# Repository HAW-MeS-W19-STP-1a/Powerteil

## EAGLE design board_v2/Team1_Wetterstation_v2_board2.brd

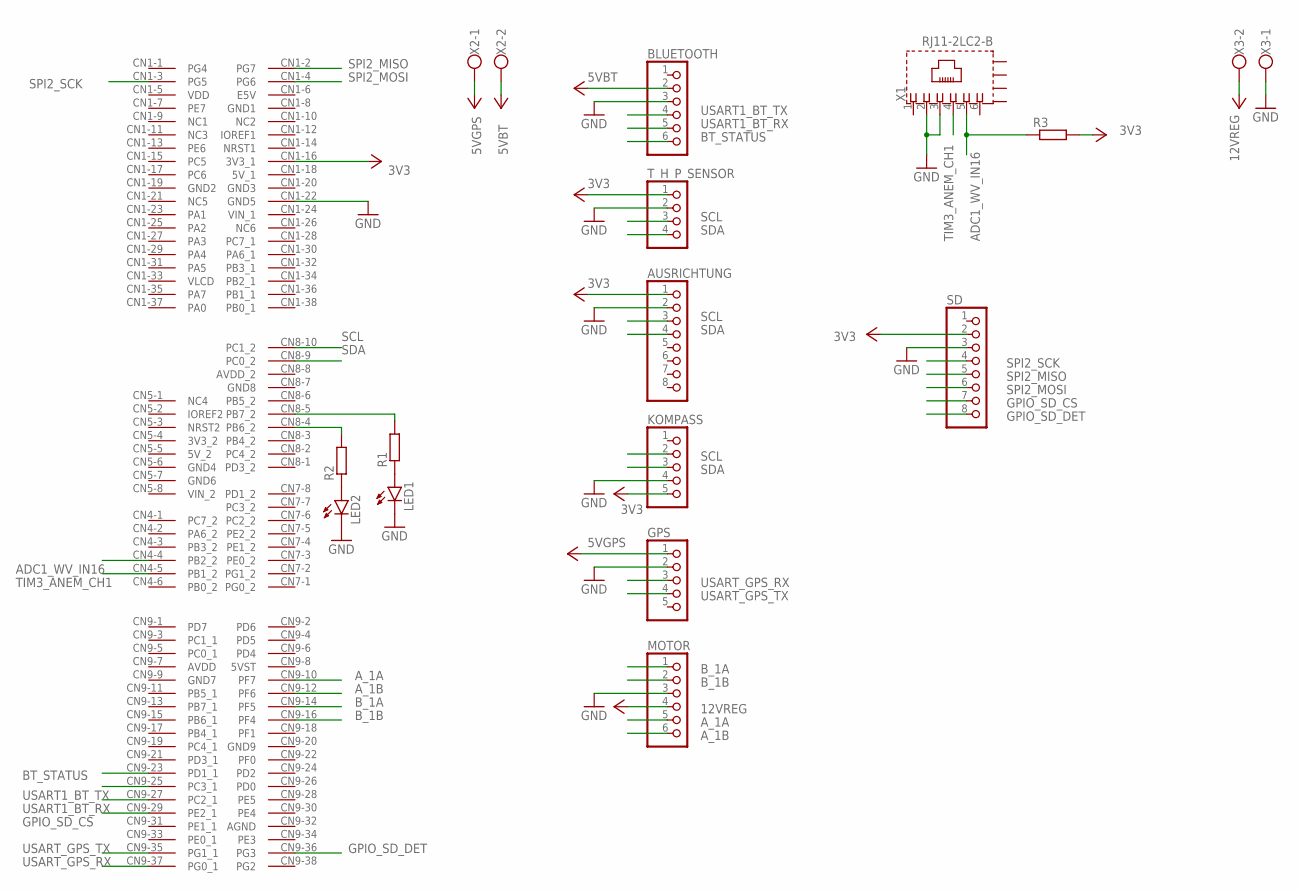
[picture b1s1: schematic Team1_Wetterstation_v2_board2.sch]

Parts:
AUSRICHTUNG: PINHD-1X8/90; 1X08/90
BLUETOOTH: PINHD-1X6/90; 1X06/90
GPS: PINHD-1X5/90; 1X05/90
KOMPASS: PINHD-1X5/90; 1X05/90
LED1, LED2: LED; SMARTLED-TTW
MOTOR: PINHD-1X6/90; 1X06/90
R1, R2, R3: R-EU_R0603; R0603
SD: PINHD-1X8/90; 1X08/90
T_H_P_SENSOR: PINHD-1X4/90; 1X04/90
U$1: NUCLEO-8L152R8; MODULE_NUCLEO-L053R8
X1: RJ11-2LC2-B; RJ11-SHIELD2
X2, X3: W237-102

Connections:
3V3: AUSRICHTUNG.1, KOMPASS.5, R3.2, SD.2, T_H_P_SENSOR.1, U$1.CN1-16 (3V3_1); also elsewhere on the board
5VBT: BLUETOOTH.2, X2.2
5VGPS: GPS.1, X2.1
12VREG: MOTOR.4, X3.2
ADC1_WV_IN16: R3.1, U$1.CN4-4 (PB2_2), X1.5
A_1A: MOTOR.5, U$1.CN9-10 (PF7)
A_1B: MOTOR.6, U$1.CN9-12 (PF6)
BT_STATUS: BLUETOOTH.6, U$1.CN9-23 (PD1_1)
B_1A: MOTOR.1, U$1.CN9-14 (PF5)
B_1B: MOTOR.2, U$1.CN9-16 (PF4)
GND: AUSRICHTUNG.2, BLUETOOTH.3, GPS.2, KOMPASS.4, LED1.C@1 (C), LED2.C@1 (C), MOTOR.3, SD.3, T_H_P_SENSOR.2, U$1.CN1-22 (GND5), X1.2, X1.3, X3.1; also elsewhere on the board
GPIO_SD_CS: SD.7, U$1.CN9-29 (PE2_1); also elsewhere on the board
GPIO_SD_DET: SD.8, U$1.CN9-36 (PG3); also elsewhere on the board
unnamed: R1.2, U$1.CN8-5 (PB7_2)
unnamed: LED1.A@1 (A), R1.1
unnamed: R2.2, U$1.CN8-4 (PB6_2)
unnamed: LED2.A@1 (A), R2.1
SCL: AUSRICHTUNG.3, KOMPASS.2, T_H_P_SENSOR.3, U$1.CN8-10 (PC1_2)
SDA: AUSRICHTUNG.4, KOMPASS.3, T_H_P_SENSOR.4, U$1.CN8-9 (PC0_2)
SPI2_MISO: SD.5, U$1.CN1-2 (PG7); also elsewhere on the board
SPI2_MOSI: SD.6, U$1.CN1-4 (PG6); also elsewhere on the board
SPI2_SCK: SD.4, U$1.CN1-3 (PG5); also elsewhere on the board
TIM3_ANEM_CH1: U$1.CN4-5 (PB1_2), X1.4
USART1_BT_RX: BLUETOOTH.5, U$1.CN9-27 (PC2_1)
USART1_BT_TX: BLUETOOTH.4, U$1.CN9-25 (PC3_1)
USART_GPS_RX: GPS.3, U$1.CN9-37 (PG0_1)
USART_GPS_TX: GPS.4, U$1.CN9-35 (PG1_1)

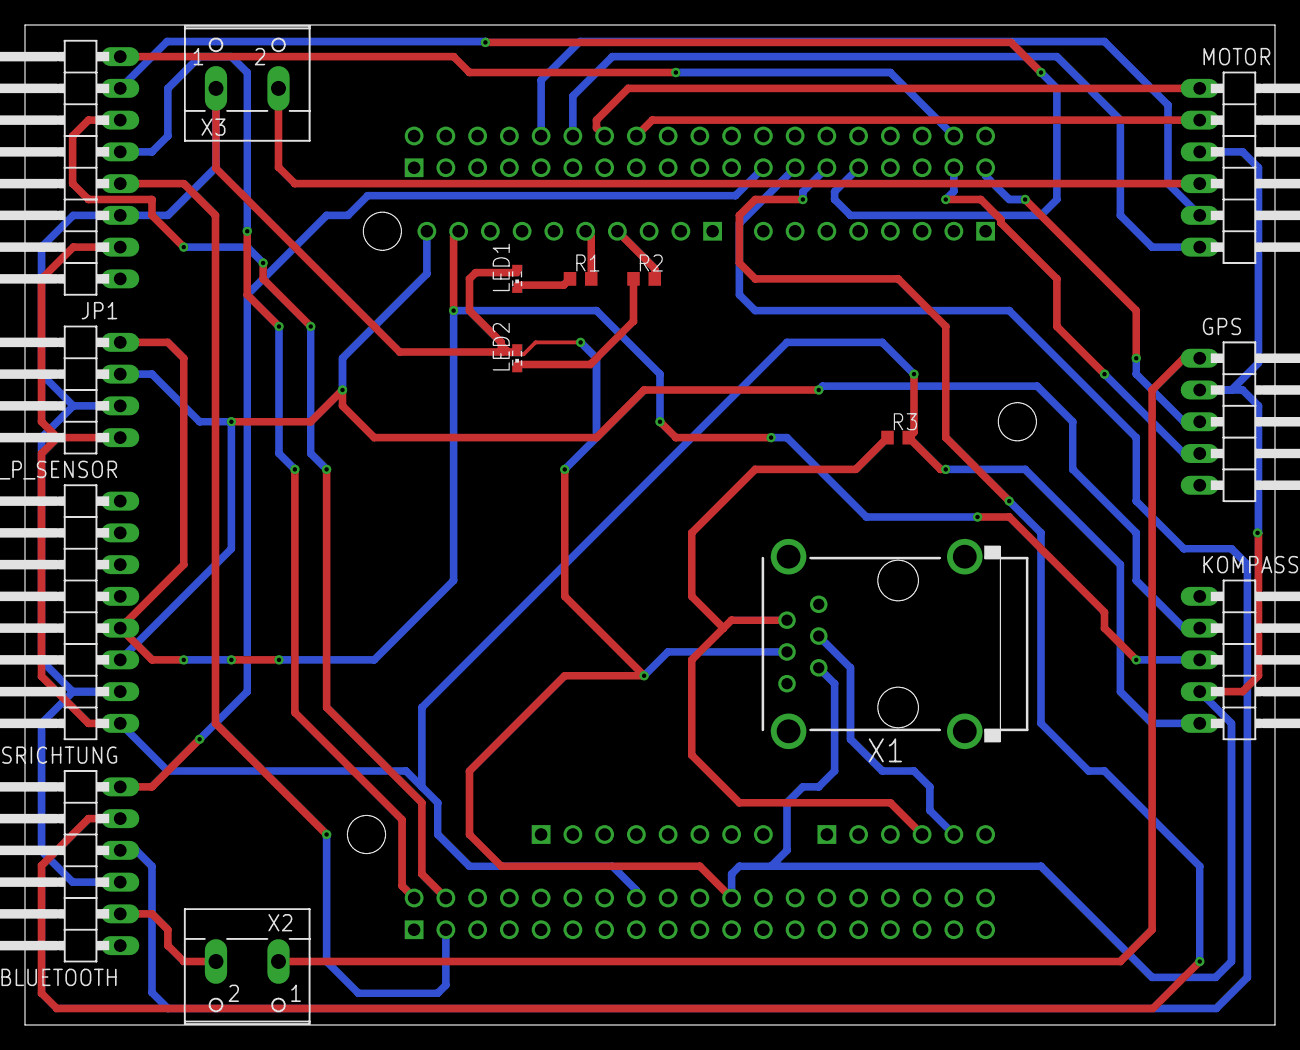
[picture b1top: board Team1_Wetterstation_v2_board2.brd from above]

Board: 2 copper layers, 100.0 x 80.0 mm, 16 parts (0 on the bottom side), 27 nets.

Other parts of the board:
JP1: 1X08/90

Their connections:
3V3: JP1.2; also elsewhere on the board
GND: JP1.3; also elsewhere on the board
GPIO_SD_CS: JP1.7; also elsewhere on the board
GPIO_SD_DET: JP1.8; also elsewhere on the board
SPI2_MISO: JP1.5; also elsewhere on the board
SPI2_MOSI: JP1.6; also elsewhere on the board
SPI2_SCK: JP1.4; also elsewhere on the board

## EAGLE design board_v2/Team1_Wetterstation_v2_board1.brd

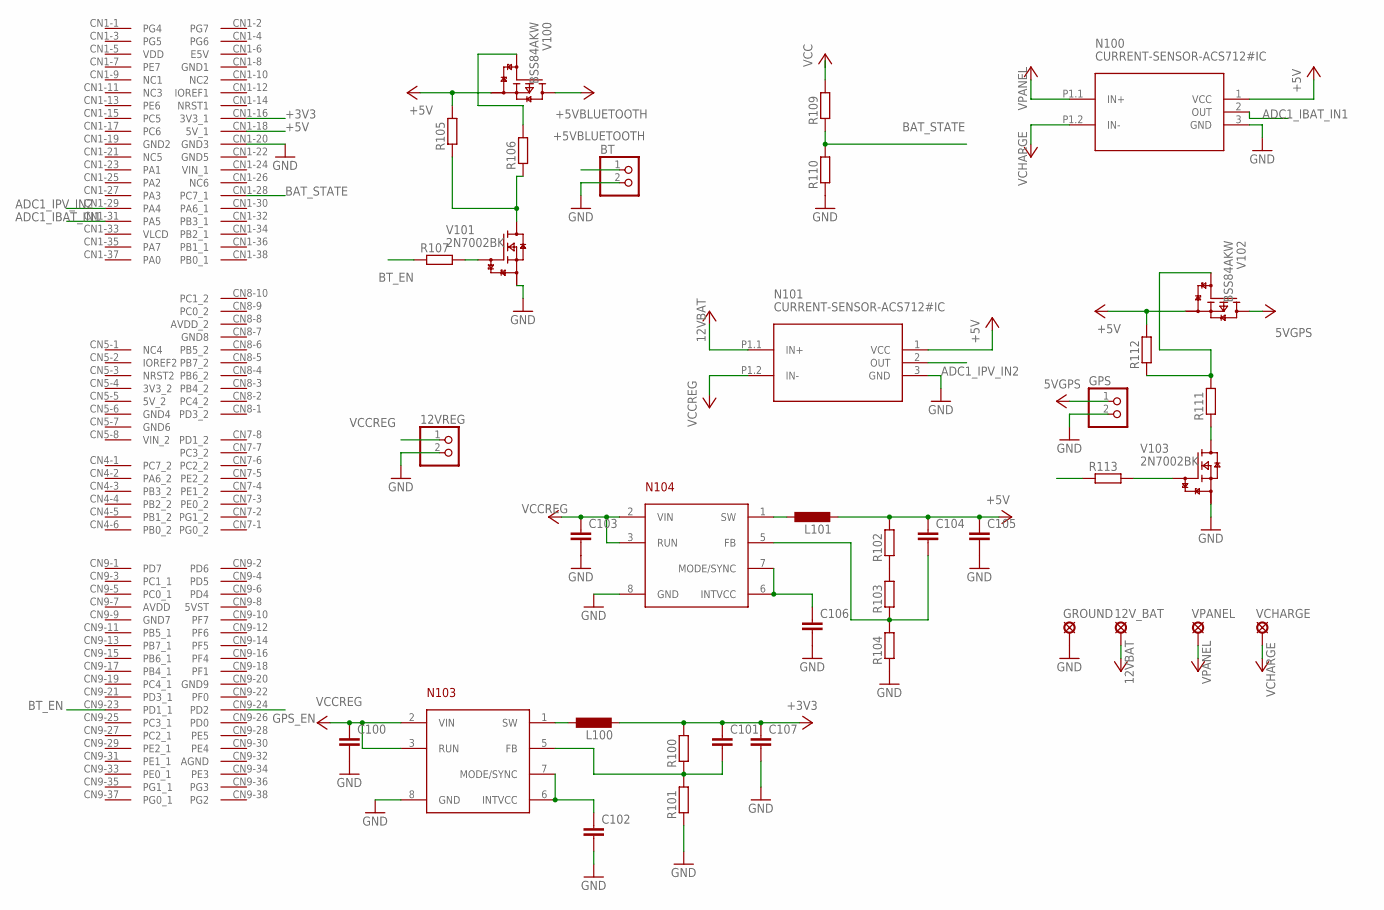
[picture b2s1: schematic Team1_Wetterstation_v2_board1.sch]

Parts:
12VREG: PINHD-1X2; 1X02
12V_BAT: SE14
BT: PINHD-1X2; 1X02
C100, C101, C102, C103, C104, C105, C106, C107: C-EUC0603; C0603
GPS: PINHD-1X2; 1X02
GROUND: SE14
L100, L101: L-EU0207/5V; 0207/5V
N100, N101: CURRENT-SENSOR-ACS712#IC
N103, N104: LTC3621; LTC3621FP
R100, R101, R102, R103, R104, R111, R112, R113: R-EU_R0603; R0603
R105, R110: 100k; R0603
R106, R107: 1k; R0603
R109: 270k; R0603
U$1: NUCLEO-8L152R8; MODULE_NUCLEO-L053R8
V100, V102: BSS84AKW; SOT323
V101, V103: 2N7002BK; SOT23
VCHARGE: SE14
VPANEL: SE14

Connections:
5VGPS: GPS.1, V102.3 (D)
12VBAT: 12V_BAT.MP, N101.P1.1 (IN+), R109.2
+3V3: C101.1, C107.1, L100.2, R100.2, U$1.CN1-16 (3V3_1)
+5V: C104.1, C105.1, L101.2, N100.1 (VCC), N101.1 (VCC), R102.2, R105.2, R112.2, U$1.CN1-18 (5V_1), V100.2 (S), V102.2 (S)
+5VBLUETOOTH: BT.1, V100.3 (D)
ADC1_IBAT_IN1: N100.2 (OUT), U$1.CN1-31 (PA5)
ADC1_IPV_IN2: N101.2 (OUT), U$1.CN1-29 (PA4)
BAT_STATE: R109.1, R110.2, U$1.CN1-28 (PC7_1)
BT_EN: R107.1, U$1.CN9-23 (PD1_1)
GND: 12VREG.2, BT.2, C100.2, C102.2, C103.2, C105.2, C106.2, C107.2, GPS.2, GROUND.MP, N100.3 (GND), N101.3 (GND), N103.8 (GND), N104.8 (GND), R101.1, R104.1, R110.1, U$1.CN1-20 (GND3), V101.2 (S), V103.2 (S)
GPS_EN: R113.1, U$1.CN9-24 (PD2)
unnamed: R106.2, V100.1 (G)
unnamed: C102.1, N103.6 (INTVCC), N103.7 (MODE/SYNC)
unnamed: R107.2, V101.1 (G)
unnamed: R105.1, R106.1, V101.3 (D)
unnamed: L100.1, N103.1 (SW)
unnamed: L101.1, N104.1 (SW)
unnamed: C101.2, N103.5 (FB), R100.1, R101.2
unnamed: C106.1, N104.6 (INTVCC), N104.7 (MODE/SYNC)
unnamed: R102.1, R103.2
unnamed: C104.2, N104.5 (FB), R103.1, R104.2
unnamed: R113.2, V103.1 (G)
unnamed: R111.1, V103.3 (D)
unnamed: R111.2, R112.1, V102.1 (G)
VCCREG: 12VREG.1, C100.1, C103.1, N101.P1.2 (IN-), N103.2 (VIN), N103.3 (RUN), N104.2 (VIN), N104.3 (RUN)
VCHARGE: N100.P1.2 (IN-), VCHARGE.MP
VPANEL: N100.P1.1 (IN+), VPANEL.MP

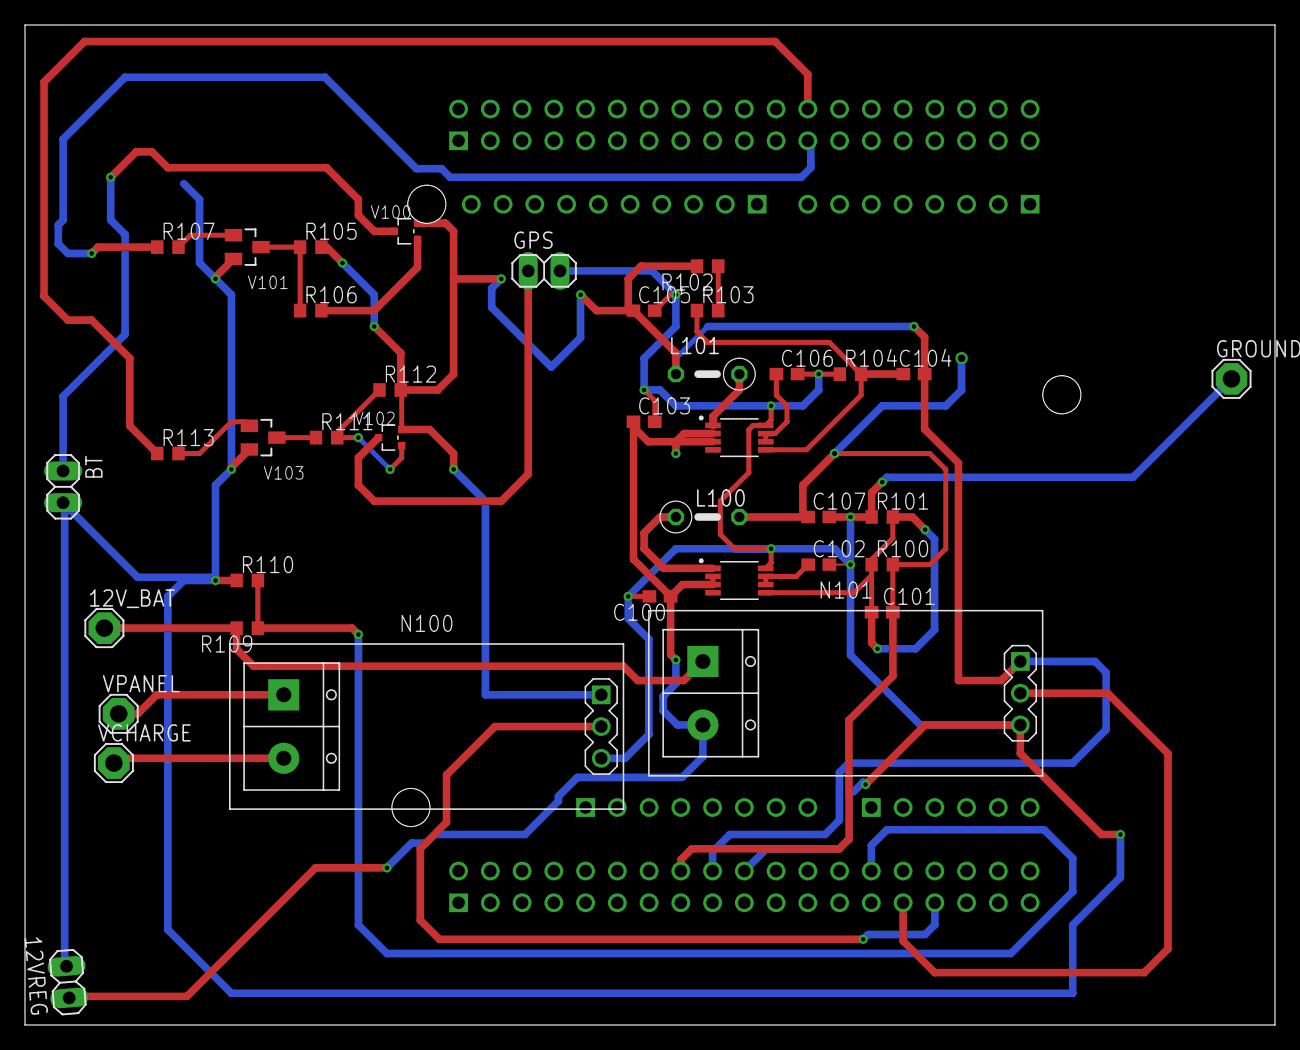
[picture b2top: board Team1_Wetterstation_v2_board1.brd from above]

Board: 2 copper layers, 100.0 x 80.0 mm, 39 parts (0 on the bottom side), 27 nets.

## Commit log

2019-11-18 Stromlaufplan
2019-11-19 Kopie für EAGLE Vers. 7
2019-11-25 Korrektur
2019-11-26 Board Layout v1. Bibliothek hinzugefügt

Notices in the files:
parts and their libraries:
diy-modules: Released under the Creative Commons Attribution 4.0 International License: http://creativecommons.org/licenses/by/4.0
